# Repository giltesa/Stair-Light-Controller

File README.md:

# Stair Light - Controller [IN PROGRESS]

This project contain 3 boards for making a LED light controller for using with stairs, corridors, or anything where people can cross, and you want to control light effects automatically.

Boards:

1. Stair Light - Controller
2. Stair Light - Controller MicroSD/USB-C
3. Stair Light - Controller PSU

These boards are made for install them inside a BHT-100GA thermostat. I think It can be difficult to find it now, because I bought it 5 years ago for making a WiFi thermostat but finally I discarded my initially idea.

Anyway, you can use the circuit in your own case if you want.

The circuit contains a ESP32 as microcontroller and WiFi/Bluetooth communication, it also has a RS485 controller to connect to the slave sensors to detect people who cross. This is the full list specification:

- **Microcontroller**: ESP32-WROOM / ESP32-WROVER-B (with auto-boot).
- **Communications**: WiFi, Bluetooth, RS485 3V3.
- **Programming port**: USB-C by CP2104.
- **User interface**: IPS round screen, LED status, Switches: Buzzer, Menu, Up, Down, Ok, Reset and Boot.
- **Storage**: MicroSD
- **Others**:
  - Real time clock DS3231 with li-ion battery LIR2032 (or not rechargeable CR2032).
  - Temperature and humidity sensor HTU21D
  - External connector to connect the PSU board (power, NeoPixel and RS485 communication).

## License

This project is licensed under a **Creative Commons** license:
**[Attribution-NonCommercial-ShareAlike 4.0 International (CC BY-NC-SA 4.0) ](https://creativecommons.org/licenses/by-nc-sa/4.0/)**

Check the [LICENSE.md](LICENSE.md) for more information.

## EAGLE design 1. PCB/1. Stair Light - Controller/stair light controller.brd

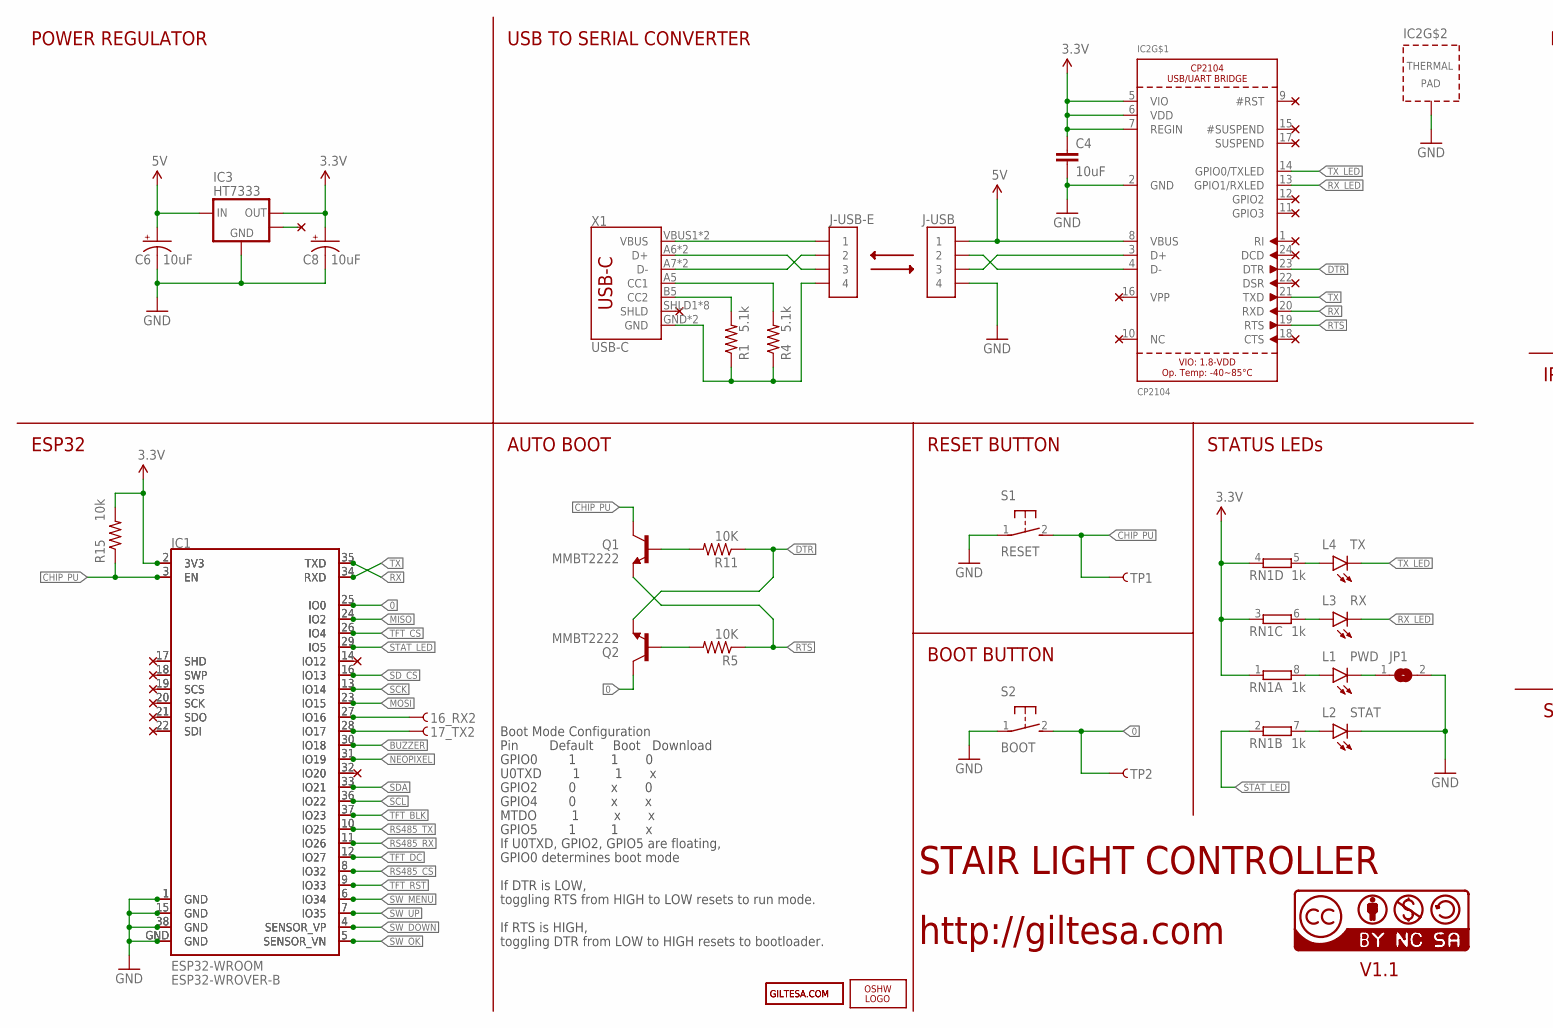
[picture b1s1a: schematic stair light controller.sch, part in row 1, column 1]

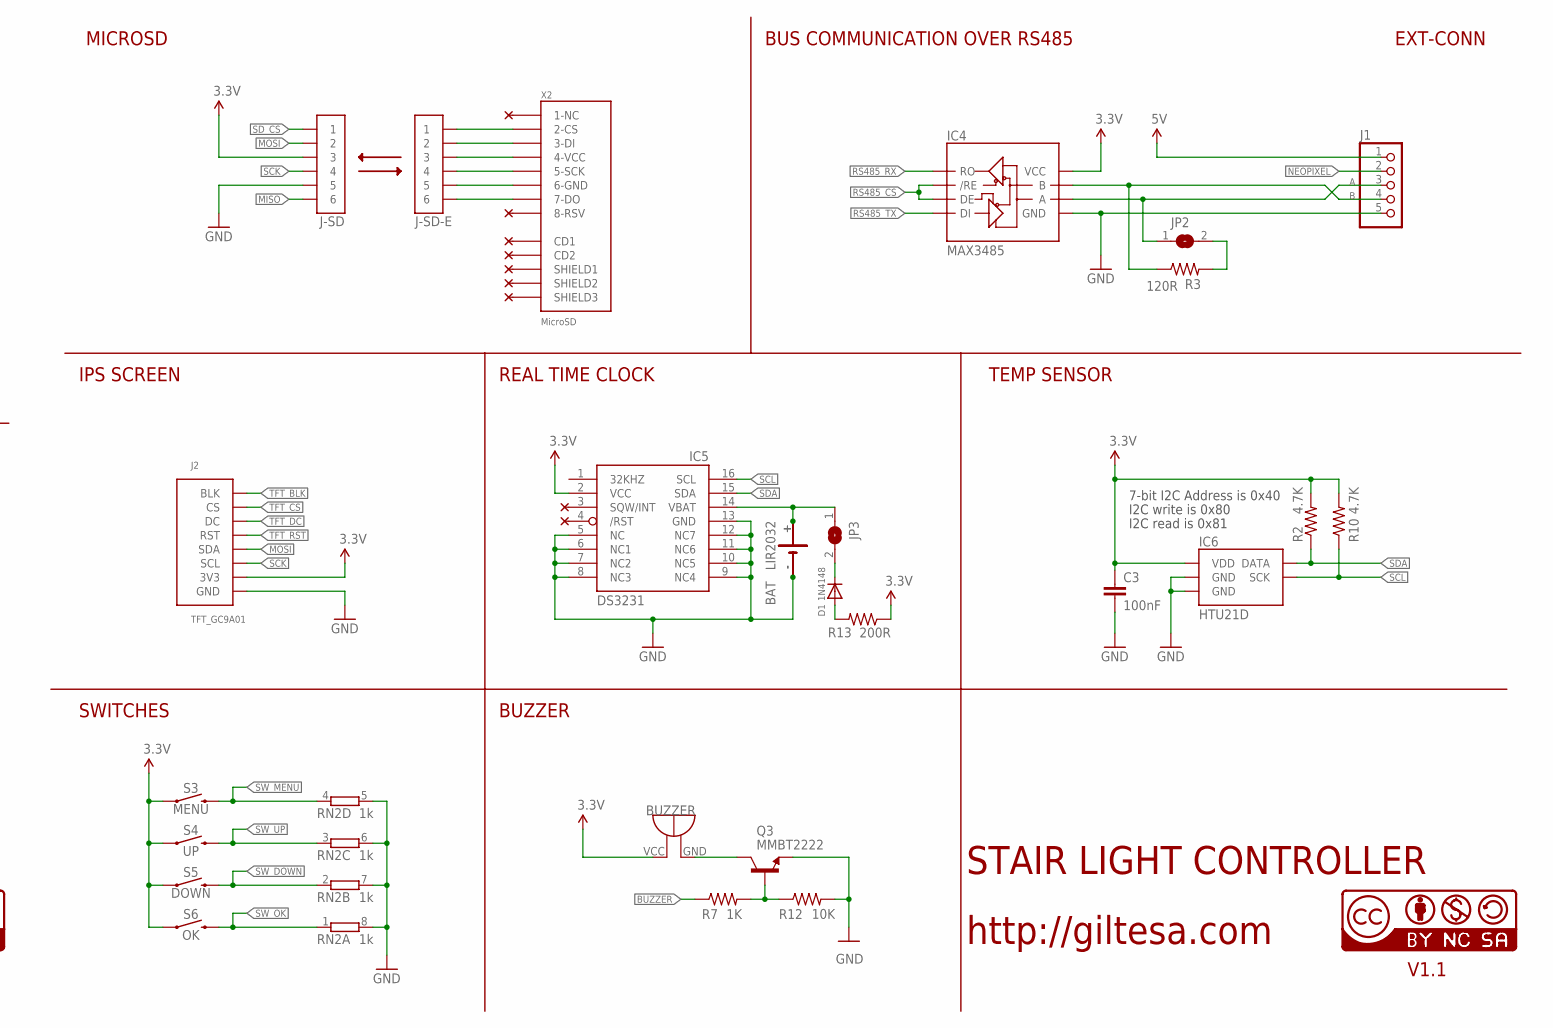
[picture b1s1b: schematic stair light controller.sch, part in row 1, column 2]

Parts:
16_RX2, 17_TX2: TEST-POINTTP_15TH_THRU; TP_15TH
BAT: LIR2032; LIR2032_SMD
BUZZER: BUZZER_9MM
C3: 100nF; C0603
C4: 10uF; C0805
C6, C8: 10uF; EIA3216
D1: 1N4148; SOD-123
IC1: ESP32-WROVER-B
IC2: CP2104; QFN24_4MM_SMSC
IC3: HT7333; SOT89_1
IC4: MAX3485; SO08
IC5: DS3231; SO16W
IC6: HTU21D
J1: PINHD-1X5; 1X05
J2: TFT_GC9A01; LCD_GC9A01
J-SD: 2X03
J-SD-E: 2X03
J-USB: 2X02
J-USB-E: 2X02
JP1, JP3: JUMPER-SMD0402; JUMPER-SMD_0402
JP2: JUMPER-SMD0805; JUMPER-SMD
L1: PWD; LED-0603
L2: STAT; LED-0603
L3: RX; LED-0603
L4: TX; LED-0603
LOGO1: OSHW_LOGO_FILLX0150-NT; OSHW_FILLX150_NOTEXT
Q1, Q2: MMBT2222; SOT23-3
Q3: MMBT2222; SOT23
R1, R4: 5.1k; R0603
R2, R10: 4.7K; R0603
R3: 120R; R0603
R5, R11, R12: 10K; R0603
R7: 1K; R0603
R13: 200R; R0603
R15: 10k; R0603
RN1, RN2: 1k; 0603-ARV
S1: RESET; SWITCH_SMD_4.6X2.8MM
S2: BOOT; SWITCH_SMD_4.6X2.8MM
S3: MENU; TACTILE_SWITCH_SMD_6.2MM_TALL
S4: UP; TACTILE_SWITCH_SMD_6.2MM_TALL
S5: DOWN; TACTILE_SWITCH_SMD_6.2MM_TALL
S6: OK; TACTILE_SWITCH_SMD_6.2MM_TALL
TP1, TP2: TEST-POINTTP_15TH_THRU; TP_15TH
U1": ESP32-WROOM; ESP32-WROOM-NARROW
U$5: CR2032SMT; CR2032
U$9, U$26: CC-NC-BCNIX; CC-NC-B_NIX
U$10: GILTESA.COM_COPPER
U$13: GILTESA.COM_MASK
X1: USB-C; USB-C-16P
X2: MicroSD; MICROSD_2

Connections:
0: IC1.25 (IO0), Q2.3 (C), S2.2 (B), TP2.P$1, U1".25 (IO0)
3.3V: BUZZER.VCC, C3.1, C4.1, C8.A (+), IC1.2 (3V3), IC2.5 (VIO), IC2.6 (VDD), IC2.7 (REGIN), IC3.3 (OUT), IC4.8 (VCC), IC5.2 (VCC), IC6.VDD, J2.3V3, J2.3V3" (3V3), J-SD.3, R2.2, R10.2, R13.1, R15.2, RN1.1, RN1.3 (1), RN1.4 (1), S3.A2 (1), S4.A2 (1), S5.A2 (1), S6.A2 (1), U1".2 (3V3)
5V: C6.A (+), IC2.8 (VBUS), IC3.2 (IN), J1.1, J-USB.1
12: IC1.14 (IO12), U1".14 (IO12)
16_NOT_DEV_PCB_RX2: 16_RX2.P$1, IC1.27 (IO16), U1".27 (IO16)
17_NOT_DEV_PCB_TX2: 17_TX2.P$1, IC1.28 (IO17), U1".28 (IO17)
A: IC4.6 (A), J1.3, JP2.1
B: IC4.7 (B), J1.4, R3.1
BUZZER: IC1.30 (IO18), R7.1, U1".30 (IO18)
CHIP_PU: IC1.3 (EN), Q1.3 (C), R15.1, S1.2 (B), TP1.P$1, U1".3 (EN)
D+: IC2.3 (D+), J-USB.3
D-: IC2.4 (D-), J-USB.2
DTR: IC2.23 (DTR), Q2.2 (E), R11.1
EXT_PCB_3.3V: J-SD-E.3, X2.4-VCC
EXT_PCB_5V: J-USB-E.1, X1.VBUS1 (VBUS), X1.VBUS2 (VBUS)
EXT_PCB_CC1: R4.2, X1.A5 (CC1)
EXT_PCB_CC2: R1.2, X1.B5 (CC2)
EXT_PCB_D+: J-USB-E.3, X1.A6 (D+), X1.B6 (D+)
EXT_PCB_D-: J-USB-E.2, X1.A7 (D-), X1.B7 (D-)
EXT_PCB_GND: J-SD-E.5, J-USB-E.4, R1.1, R4.1, X1.GND, X1.GND2 (GND), X2.6-GND
EXT_PCB_MISO: J-SD-E.6, X2.7-DO
EXT_PCB_MOSI: J-SD-E.2, X2.3-DI
EXT_PCB_SCK: J-SD-E.4, X2.5-SCK
EXT_PCB_SD_CS: J-SD-E.1, X2.2-CS
GND: BAT.-, C3.2, C4.2, C6.C (-), C8.C (-), IC1.1 (GND), IC1.15 (GND), IC1.38 (GND), IC1.GND, IC2.2 (GND), IC2.THERM (TP), IC3.1 (GND), IC4.5 (GND), IC5.5 (NC), IC5.6 (NC1), IC5.7 (NC2), IC5.8 (NC3), IC5.9 (NC4), IC5.10 (NC5), IC5.11 (NC6), IC5.12 (NC7), IC5.13 (GND), IC6.7 (GND), IC6.GND, J1.5, J2.GND, J2.GND" (GND), J-SD.5, J-USB.4, JP1.2, L2.C, Q3.2 (E), R12.2, RN2.5 (2), RN2.6 (2), RN2.7 (2), RN2.8 (2), S1.1 (A), S2.1 (A), U1".1 (GND), U1".15 (GND), U1".38 (GND), U1".GND, U$5.-
MISO: IC1.24 (IO2), J-SD.6, U1".24 (IO2)
MOSI: IC1.23 (IO15), J2.SDA, J2.SDA" (SDA), J-SD.2, U1".23 (IO15)
unnamed: L1.A, RN1.8 (2)
unnamed: L2.A, RN1.7 (2)
unnamed: BAT.+, IC5.14 (VBAT), JP3.1, U$5.+
unnamed: D1.A, R13.2
unnamed: L4.A, RN1.5 (2)
unnamed: L3.A, RN1.6 (2)
unnamed: JP1.1, L1.C
unnamed: JP2.2, R3.2
unnamed: Q3.1 (B), R7.2, R12.1
unnamed: IC1.32 (IO20), U1".32 (IO20)
unnamed: BUZZER.GND, Q3.3 (C)
unnamed: IC1.20 (SCK), U1".20 (SCK)
unnamed: IC1.19 (SCS), U1".19 (SCS)
unnamed: IC1.22 (SDI), U1".22 (SDI)
unnamed: IC1.21 (SDO), U1".21 (SDO)
unnamed: IC1.17 (SHD), U1".17 (SHD)
unnamed: IC1.18 (SWP), U1".18 (SWP)
unnamed: D1.C, JP3.2
unnamed: Q1.1 (B), R11.2
unnamed: Q2.1 (B), R5.2
NEOPIXEL: IC1.31 (IO19), J1.2, U1".31 (IO19)
RS485_CS: IC1.8 (IO32), IC4.2 (/RE), IC4.3 (DE), U1".8 (IO32)
RS485_RX: IC1.11 (IO26), IC4.1 (RO), U1".11 (IO26)
RS485_TX: IC1.10 (IO25), IC4.4 (DI), U1".10 (IO25)
RTS: IC2.19 (RTS), Q1.2 (E), R5.1
RX: IC1.35 (TXD), IC2.20 (RXD), U1".35 (TXD)
RX_LED: IC2.13 (GPIO1/RXLED), L3.C
SCK: IC1.13 (IO14), J2.SCL, J2.SCL" (SCL), J-SD.4, U1".13 (IO14)
SCL: IC1.36 (IO22), IC5.16 (SCL), IC6.SCK, R10.1, U1".36 (IO22)
SDA: IC1.33 (IO21), IC5.15 (SDA), IC6.DATA, R2.1, U1".33 (IO21)
SD_CS: IC1.16 (IO13), J-SD.1, U1".16 (IO13)
STAT_LED: IC1.29 (IO5), RN1.2 (1), U1".29 (IO5)
SW_DOWN: IC1.4 (SENSOR_VP), RN2.2 (1), S5.B2 (2), U1".4 (SENSOR_VP)
SW_MENU: IC1.6 (IO34), RN2.4 (1), S3.B2 (2), U1".6 (IO34)
SW_OK: IC1.5 (SENSOR_VN), RN2.1, S6.B2 (2), U1".5 (SENSOR_VN)
SW_UP: IC1.7 (IO35), RN2.3 (1), S4.B2 (2), U1".7 (IO35)
TFT_BLK: IC1.37 (IO23), J2.BLK, J2.BLK" (BLK), U1".37 (IO23)
TFT_CS: IC1.26 (IO4), J2.CS, J2.CS" (CS), U1".26 (IO4)
TFT_DC: IC1.12 (IO27), J2.DC, J2.DC" (DC), U1".12 (IO27)
TFT_RST: IC1.9 (IO33), J2.RST, J2.RST" (RST), U1".9 (IO33)
TX: IC1.34 (RXD), IC2.21 (TXD), U1".34 (RXD)
TX_LED: IC2.14 (GPIO0/TXLED), L4.C

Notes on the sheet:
STAIR LIGHT CONTROLLER
http://giltesa.com
V1.1
POWER REGULATOR
USB TO SERIAL CONVERTER
REAL TIME CLOCK
If DTR is LOW,
If RTS is HIGH,
Boot Mode Configuration
Pin Default Boot Download
GPIO0 1 1 0
U0TXD 1 1 x
GPIO2 0 x 0
GPIO4 0 x x
MTDO 1 x x
GPIO5 1 1 x
If U0TXD, GPIO2, GPIO5 are floating,
GPIO0 determines boot mode
RESET BUTTON
STATUS LEDs
BOOT BUTTON
7-bit I2C Address is 0x40
I2C write is 0x80
I2C read is 0x81
TEMP SENSOR
SWITCHES
ESP32
AUTO BOOT
toggling RTS from HIGH to LOW resets to run mode.
toggling DTR from LOW to HIGH resets to bootloader.
MICROSD
EXT-CONN
IPS SCREEN
BUS COMMUNICATION OVER RS485
BUZZER

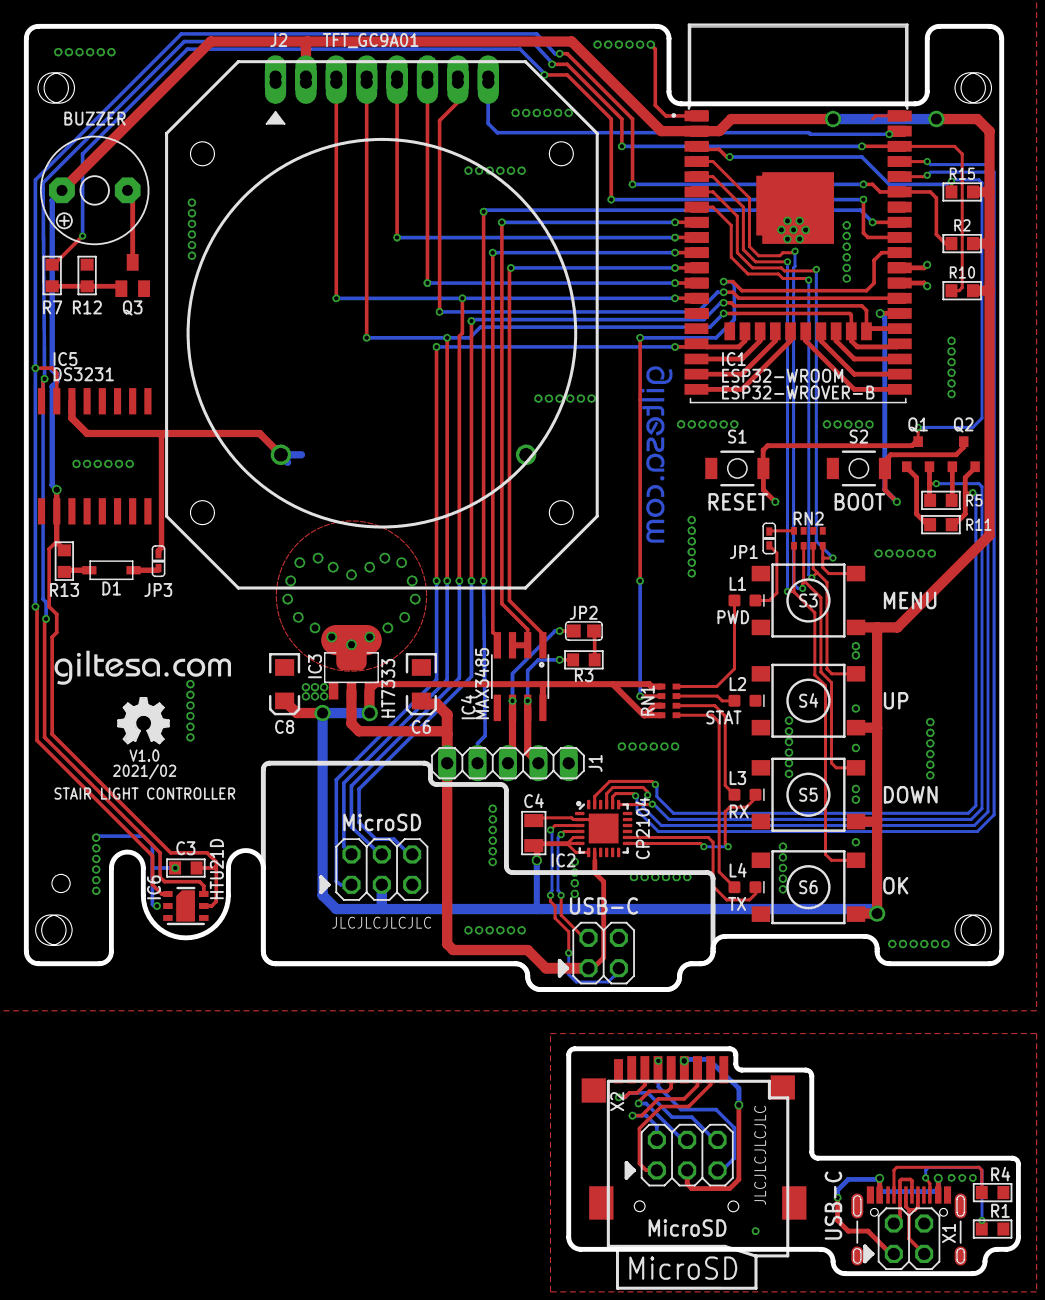
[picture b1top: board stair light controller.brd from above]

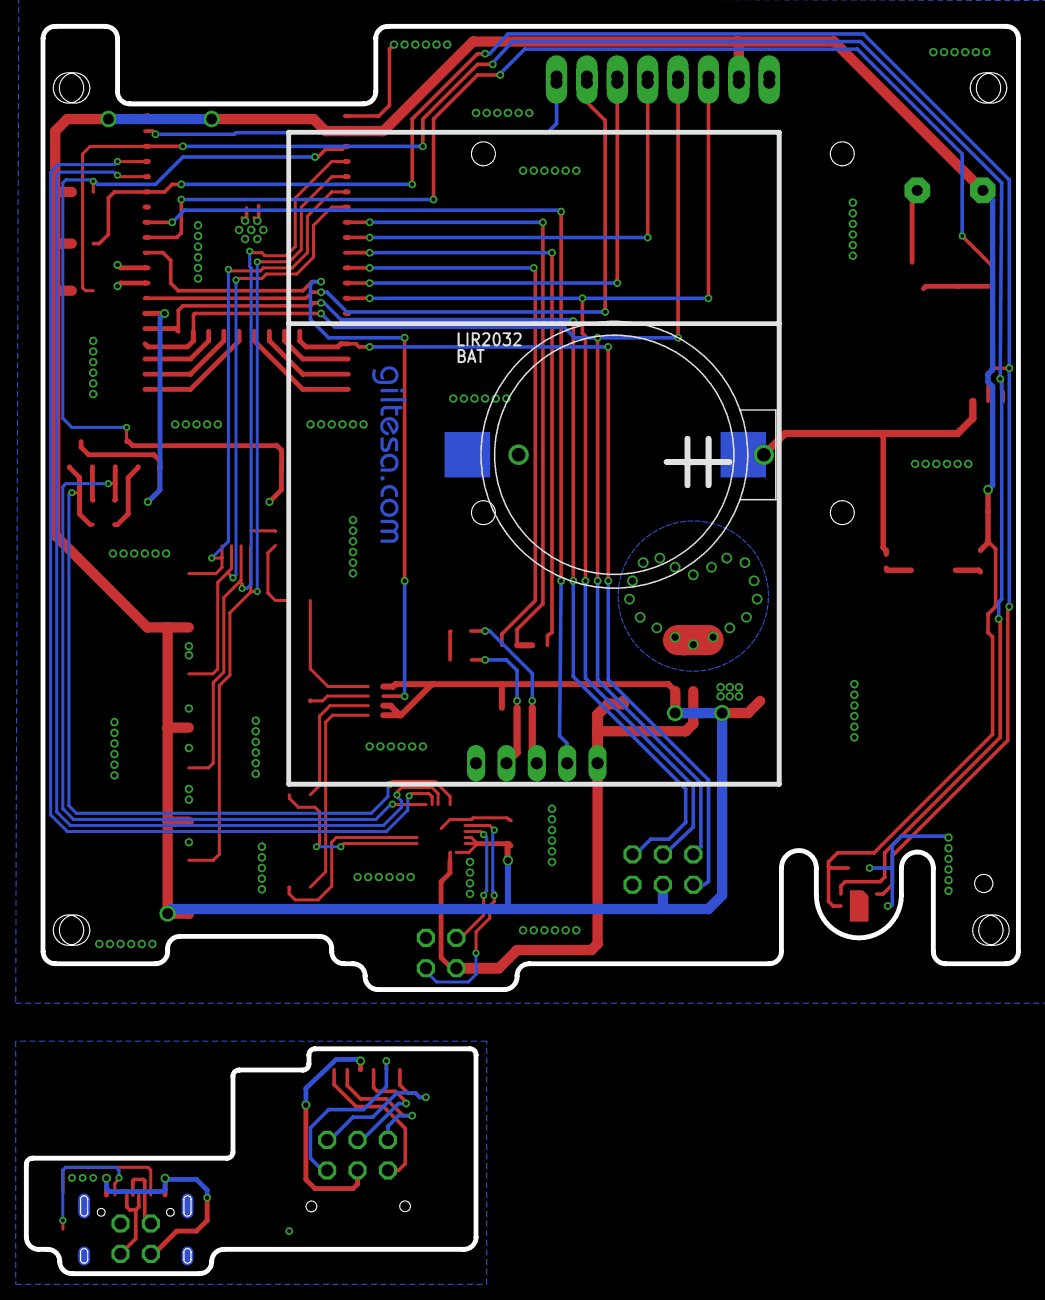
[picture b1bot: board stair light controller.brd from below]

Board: 2 copper layers, 81.5 x 80.5 mm, 61 parts (3 on the bottom side), 69 nets.

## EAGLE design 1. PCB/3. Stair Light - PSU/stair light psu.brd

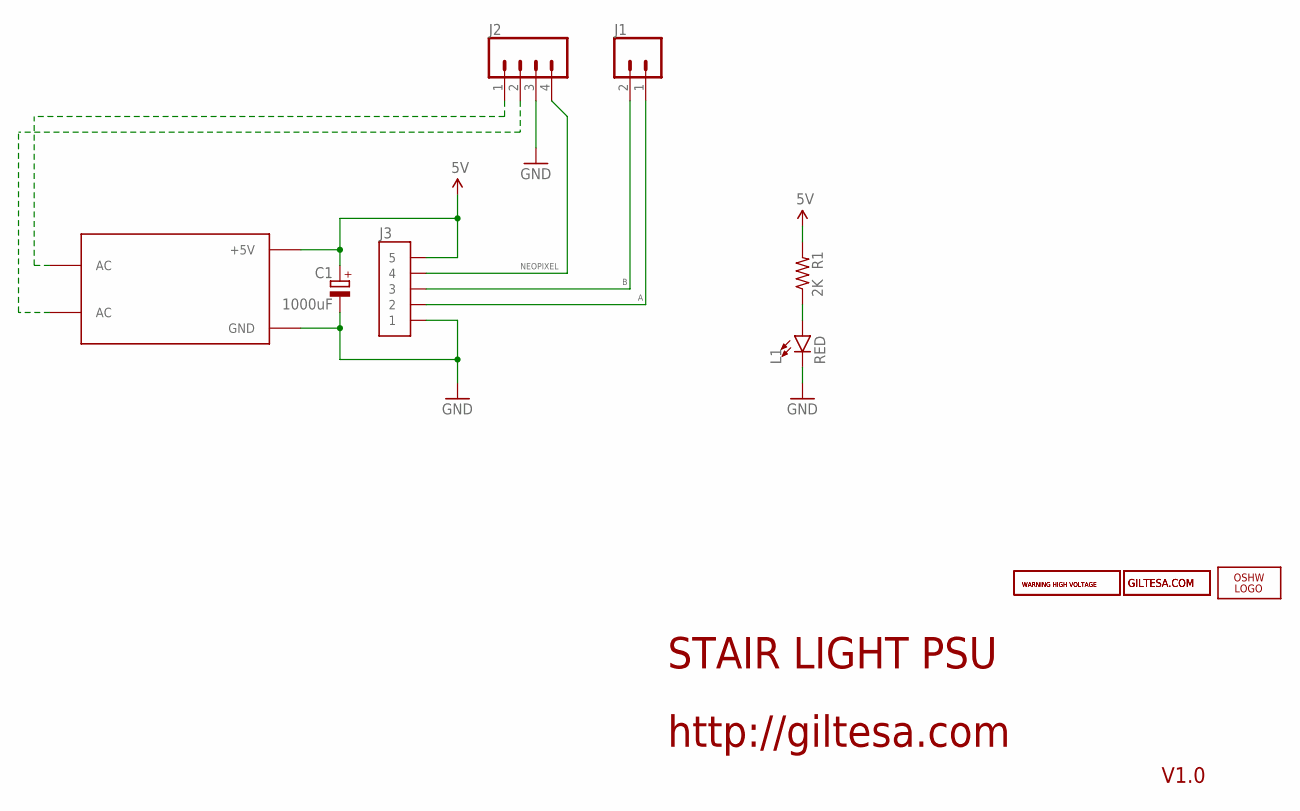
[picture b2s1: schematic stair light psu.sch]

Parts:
C1: 1000uF; B45181A
J1: TERMINAL_5MM_2P1; TERMINAL_5MM_2P
J2: TERMINAL_5MM_4P_90º_20A
J3: 1X05; 1X5_SMT_2MM
L1: RED; LED-0603
LOGO1: OSHW_LOGO_FILLX0150-NT; OSHW_FILLX150_NOTEXT
R1: 2K; R0603
U1: HILINK HLK-PM01 5V; HILINK_HLK-PM01_5V
U$3, U$6: WARNING_HIGH_VOLTAGE1; WARNING_HIGH_VOLTAGE
U$10: GILTESA.COM_COPPER
U$13: GILTESA.COM_MASK

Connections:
5V: C1.+, J3.5, R1.2, U1.+5V
A: J1.1, J3.2
B: J1.2, J3.3
GND: C1.-, J2.3, J3.1, L1.C, U1.GND
unnamed: L1.A, R1.1
unnamed: J2.1, U1.AC@2 (AC)
unnamed: J2.2, U1.AC@1 (AC)
NEOPIXEL: J2.4, J3.4

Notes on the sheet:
STAIR LIGHT PSU
http://giltesa.com
V1.0

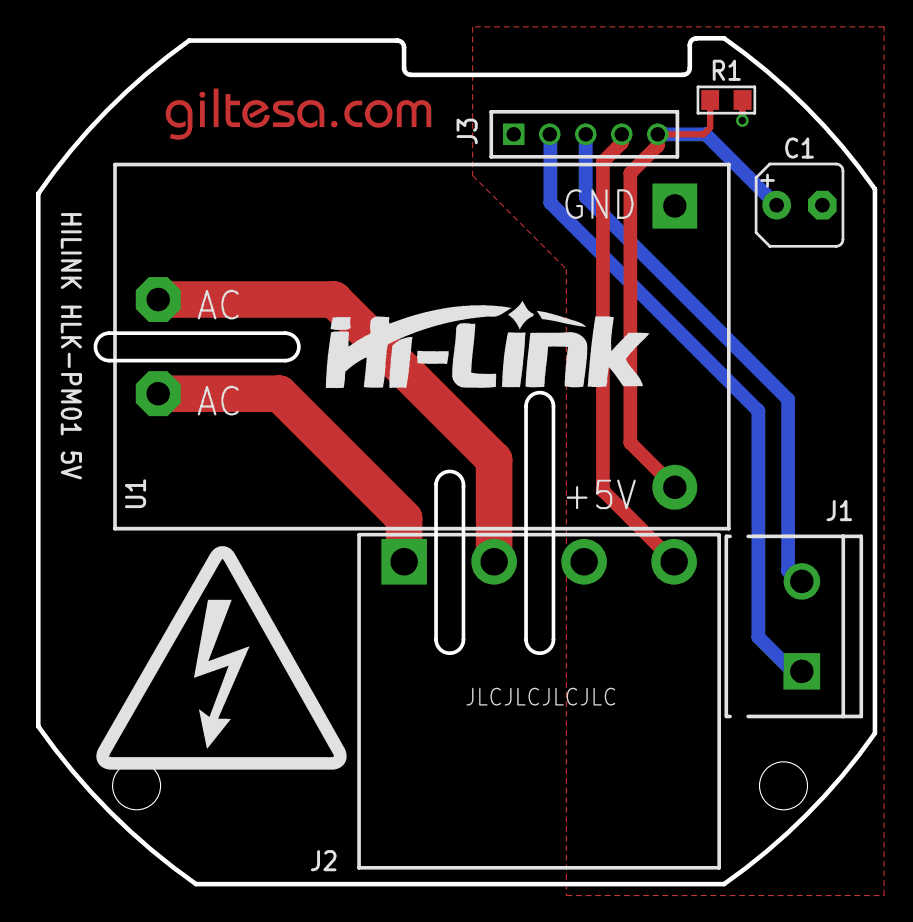
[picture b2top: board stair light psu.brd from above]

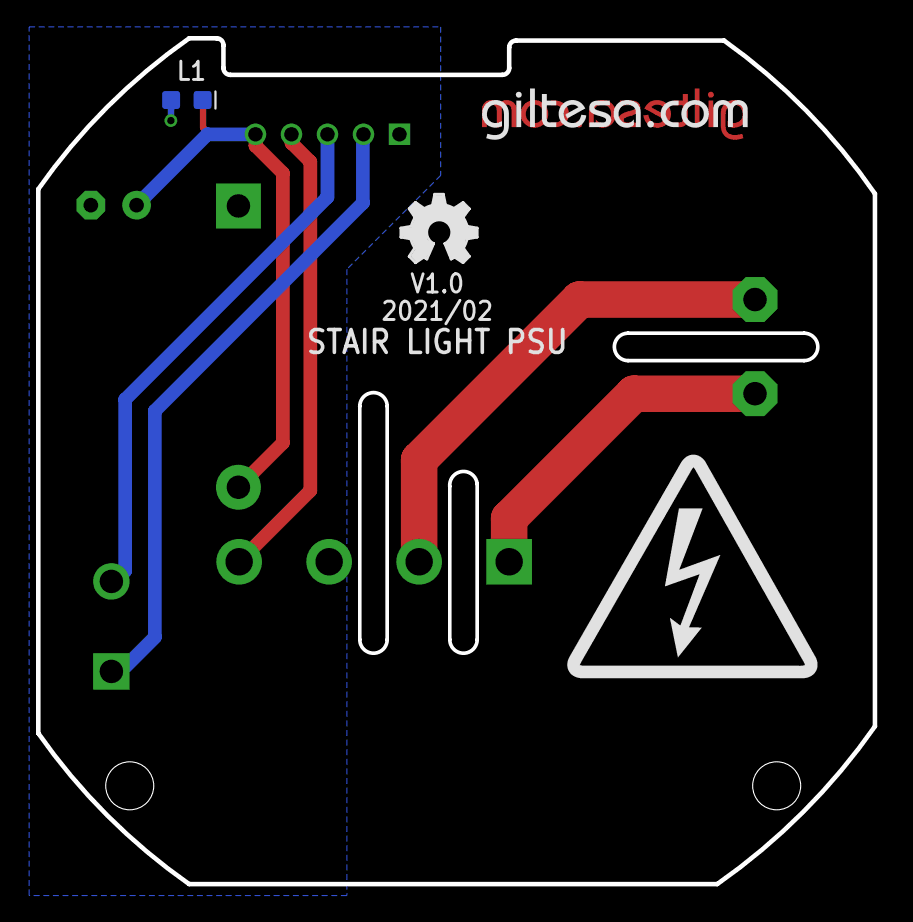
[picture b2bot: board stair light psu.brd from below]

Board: 2 copper layers, 46.5 x 47.0 mm, 12 parts (4 on the bottom side), 8 nets.

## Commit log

2021-01-23 no message
2021-01-27 Released v1.0 and sending the boards to manufacture.

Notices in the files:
parts and their libraries:
SparkFun-Switches: Licensing: Creative Commons ShareAlike 4.0 International - https://creativecommons.org/licenses/by-sa/4.0
microbuilder: This work is placed in the public domain, and may be freely used for commercial and non-commercial work with the following conditions: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
